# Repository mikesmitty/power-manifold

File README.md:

# Power Manifold

A six-port USB-C® power supply: USB Power Delivery 3.2, up to 100 W per port
from one 24 V supply, with per-port control, priority-based power sharing
and Home Assistant support. This repository holds the hardware (KiCad), the
firmware and the documentation site.

**Documentation:** <https://docs.powermanifold.io/>

- [First-time setup](https://docs.powermanifold.io/setup/first-time-setup/)
- [User guide](https://docs.powermanifold.io/guide/front-panel/)
- [Integrations](https://docs.powermanifold.io/integrations/mqtt/): MQTT,
  Home Assistant and the HTTP API
- [Hardware architecture](https://docs.powermanifold.io/developers/architecture/)

## Repository layout

| Path | Contents |
| --- | --- |
| `hardware/backplane` | Backplane KiCad project |
| `hardware/backplane-backer` | Insulating FR4 backer plate between the backplane and the rear wall |
| `hardware/charger-module` | Charger blade KiCad project |
| `hardware/controller` | Management controller card KiCad project |
| `hardware/left-side-plate` | Left chassis side plate, fabricated as a bare PCB |
| `hardware/pcie-breakout` | Pico 2 W development carrier for the management slot |
| `hardware/status-strip` | Front-panel status LED strip |
| `hardware/libraries` | Shared KiCad symbols and footprints |
| `hardware/CAD` | STEP exports of the boards |
| `firmware/controller` | Management controller firmware (RP2350) and its host tests |
| `firmware/charger-module` | Charger blade firmware (STM32G071) and its host tests |
| `firmware/update-proxy` | Cloudflare Worker that serves controller update images |
| `docs` | The documentation site (Astro and Starlight) |

Each firmware directory has a short README with build commands. Its full
developer documentation is in its `docs/` directory and is published on the
documentation site.

CI exports KiCad fabrication outputs when a board changes, and
release-please cuts a release for each component.

## License

Copyright 2024-2026 Michael Smith.

| Part | License |
| --- | --- |
| Hardware designs in `hardware/` | CERN-OHL-P-2.0 ([LICENSE-hardware](LICENSE-hardware)) |
| Documentation: Markdown files (`.md`, `.mdx`), the screenshots in `docs/src/assets/` and the site icon `docs/public/favicon.svg` | CC BY 4.0 ([LICENSE-docs](LICENSE-docs)) |
| Product renders: the images in `img/` and `docs/public/hero.webp` | None, all rights reserved |
| Everything else, including the firmware, the web page, the tools and the code of the documentation site | MIT ([LICENSE](LICENSE)) |

Third-party material keeps its own terms:

- `hardware/libraries/`: symbols, footprints and 3D models, most of them
  from the KiCad libraries, EasyEDA and part makers.
- Third-party 3D models and fonts embedded in the board files, and the
  3D models inside the board exports in `hardware/CAD/`.
- `hardware/licenses/`: the license texts for the openly licensed parts
  above, which [hardware/THIRD-PARTY.md](hardware/THIRD-PARTY.md) lists with
  their notices.
- `firmware/controller/lib/monocypher/`: CC0 or BSD-2-Clause, see its
  `LICENCE.md`.
- `firmware/tools/licenses/`: the license files of newlib and libgloss, the
  C library the firmware links, for the notices below.

Libraries that the firmware builds download, such as the Pico SDK and ST's
USB-PD stack, are not part of this repository. Each firmware release lists them in
its SBOM (`.cdx.json`) and carries their copyright notices and license texts in
a notices file (`controller-notices.txt`, `charger-module-notices.txt`).

Power Manifold is a trademark of Idle Curiosity LLC. The licenses above cover
the designs, code and documentation, not the name: a product built or modified
from this repository may say it is based on Power Manifold, but may not be sold
or distributed under that name.

USB Type-C® and USB-C® are registered trademarks of USB Implementers Forum.

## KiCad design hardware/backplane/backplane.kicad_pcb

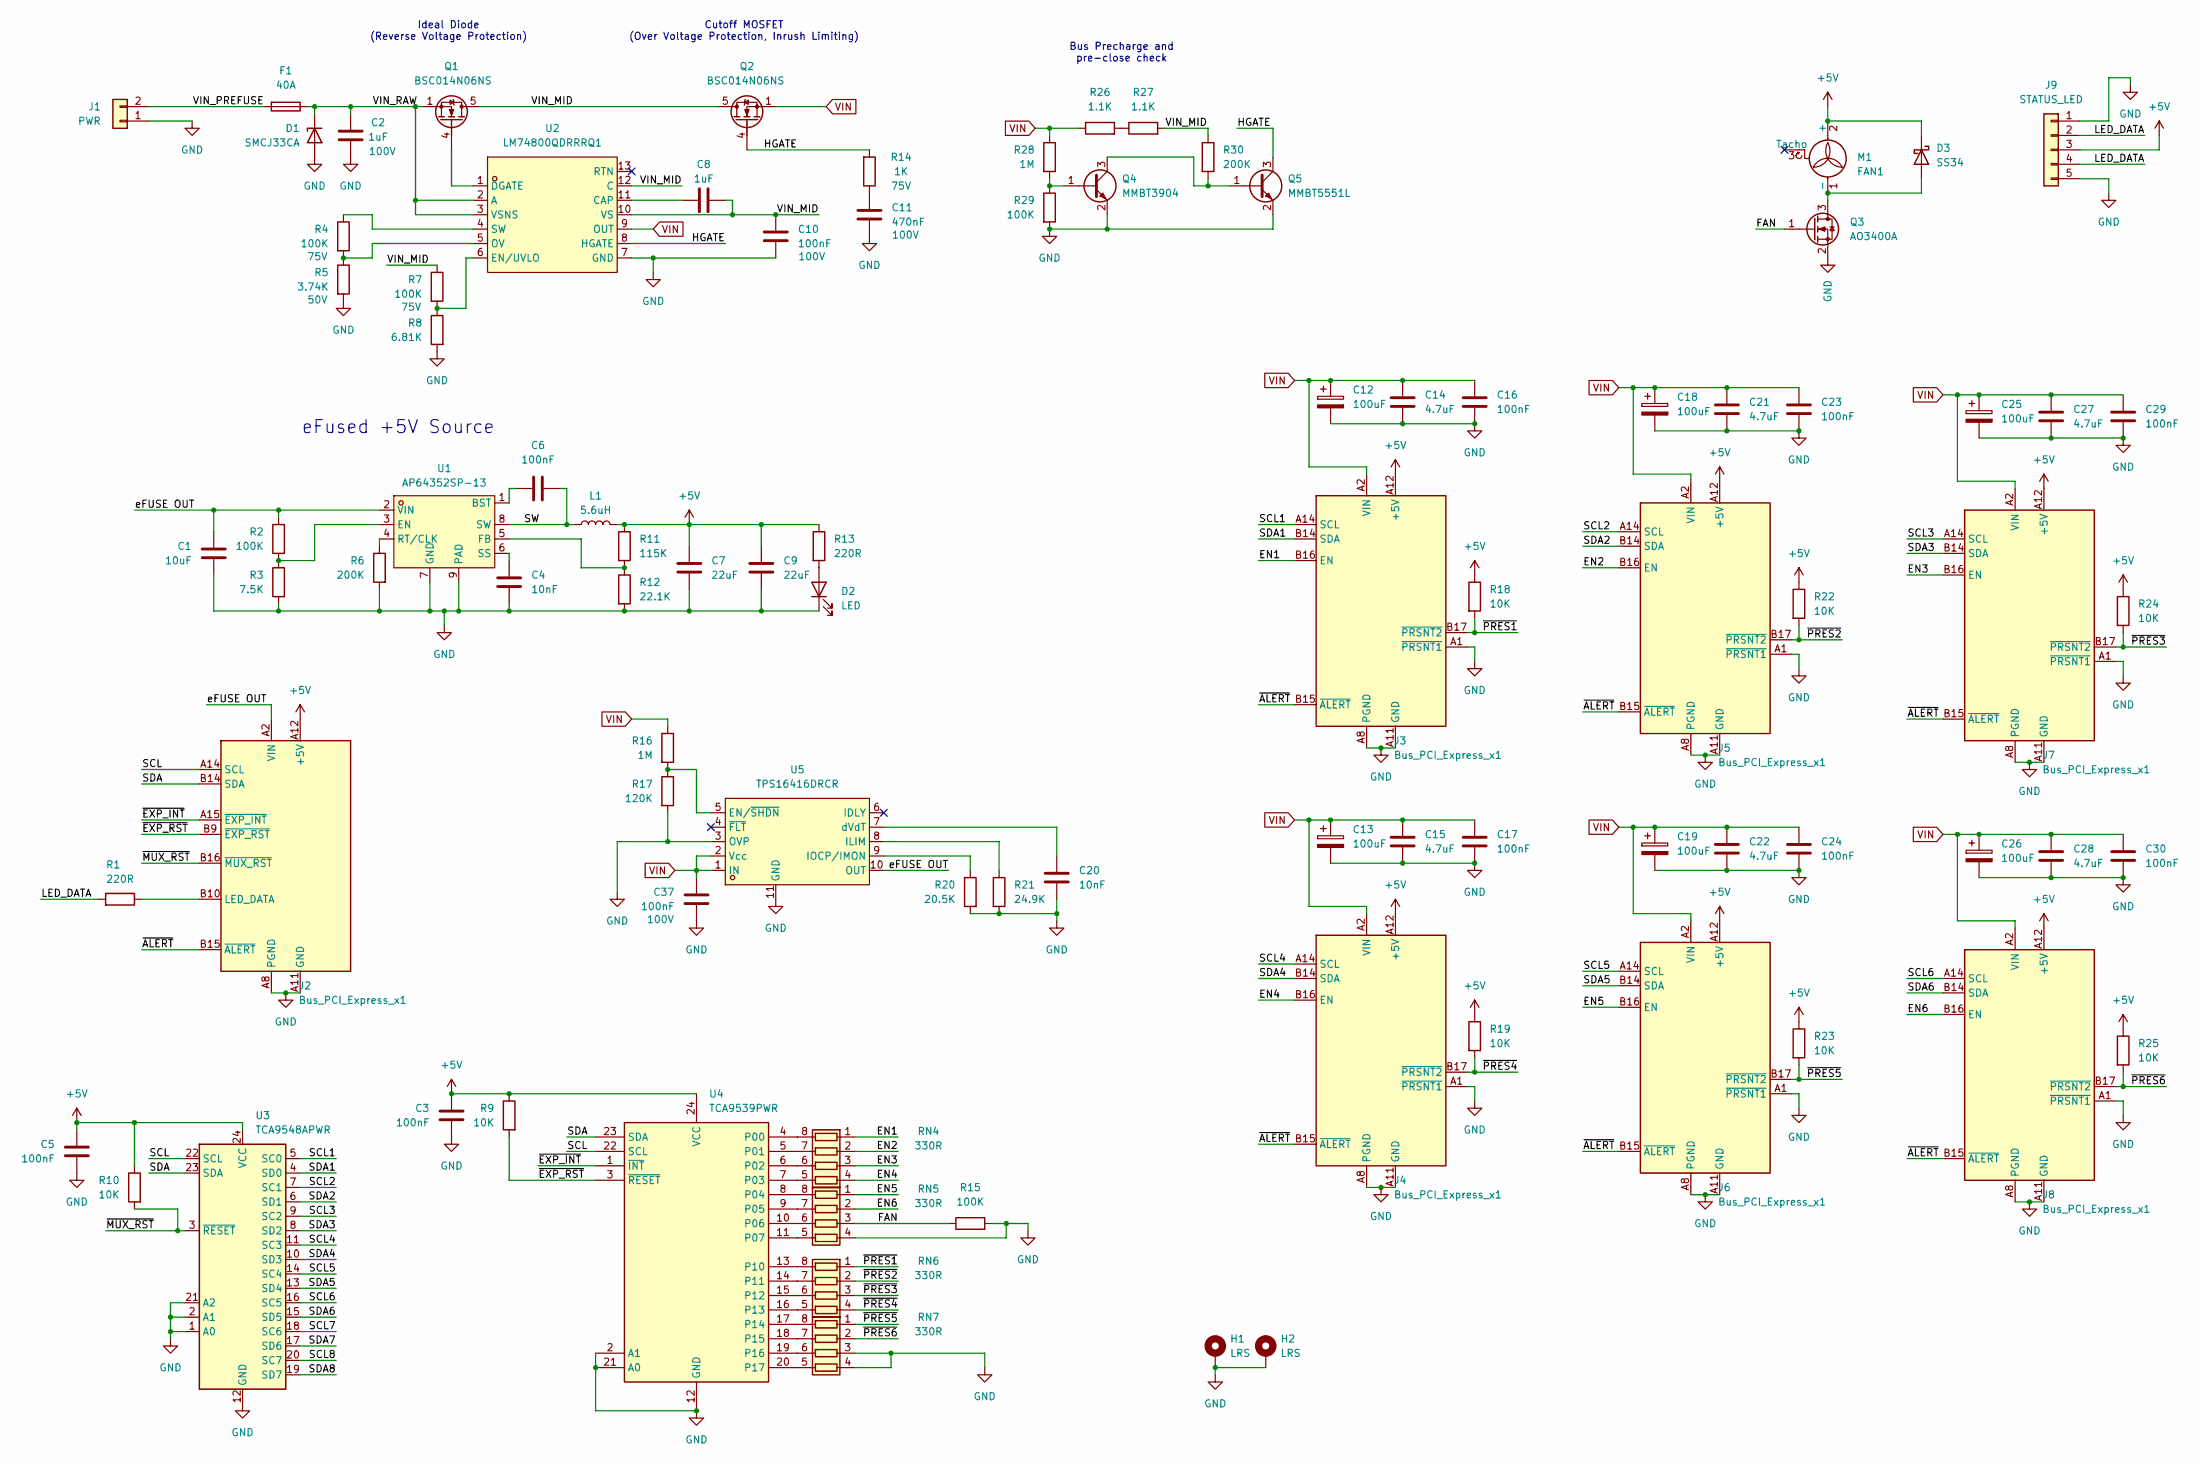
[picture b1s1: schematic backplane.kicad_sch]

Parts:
C1: 10uF; C_0805_2012Metric; LCSC C440198
C2: 1uF; C_0805_2012Metric; Voltage 100V; LCSC C5370002
C3, C5, C6, C16, C17, C23, C24, C29, C30: 100nF; C_0402_1005Metric; LCSC C307331
C4, C20: 10nF; C_0402_1005Metric; LCSC C15195
C7, C9: 22uF; C_0805_2012Metric; LCSC C45783
C8: 1uF; C_0402_1005Metric; LCSC C52923
C10, C37: 100nF; C_0603_1608Metric; Voltage 100V; LCSC C88219
C11: 470nF; C_0805_2012Metric; Voltage 100V; LCSC C596323
C12, C13, C18, C19, C25, C26: 100uF; CP_Elec_6.3x7.7; LCSC C3151829
C14, C15, C21, C22, C27, C28: 4.7uF; C_1206_3216Metric; LCSC C29823
D1: SMCJ33CA; D_SMC; LCSC C310048
D2: LED; LED_0603_1608Metric; LCSC C2286
D3: SS34; D_SMA; LCSC C8678
F1: 40A; FUSE-SMD_L6.1-W2.5; LCSC C2762486
H1, H2: LRS; MountingHole_4.3mm_M4_Pad_Via
J1: PWR; AMASS_XT60PW-M_1x02_P7.20mm_Horizontal; LCSC C98732
J2, J3, J4, J5, J6, J7, J8: Bus_PCI_Express_x1; AMPHENOL_PCI_E_10018783-10210TLF; LCSC C4693418
J9: STATUS_LED; JST_SH_BM05B-SRSS-TB_1x05-1MP_P1.00mm_Vertical; LCSC C160391
L1: 5.6uH; L_Sunlord_MWSA0603S; LCSC C408448
M1: FAN1; FanPinHeader_1x03_P2.54mm_Vertical; LCSC C234181
Q1, Q2: BSC014N06NS; Infineon_PG-TDSON-8_6.15x5.15mm; LCSC C113391
Q3: AO3400A; SOT-23; LCSC C20917
Q4: MMBT3904; SOT-23; LCSC C20526
Q5: MMBT5551L; SOT-23; LCSC C2145
R1, R13: 220R; R_0402_1005Metric; LCSC C25091
R2, R15: 100K; R_0402_1005Metric; LCSC C25741
R3: 7.5K; R_0402_1005Metric; LCSC C25918
R4, R7: 100K; R_0603_1608Metric; Voltage 75V; LCSC C25803
R5: 3.74K; R_0402_1005Metric; Voltage 50V; LCSC C15172
R6, R30: 200K; R_0402_1005Metric; LCSC C25764
R8: 6.81K; R_0603_1608Metric; LCSC C2930121
R9, R10, R18, R19, R22, R23, R24, R25: 10K; R_0402_1005Metric; LCSC C25744
R11: 115K; R_0402_1005Metric; LCSC C25747
R12: 22.1K; R_0402_1005Metric; LCSC C163478
R14: 1K; R_0603_1608Metric; Voltage 75V; LCSC C21190
R16, R28: 1M; R_0603_1608Metric; LCSC C22935
R17: 120K; R_0603_1608Metric; LCSC C25808
R20: 20.5K; R_0402_1005Metric; LCSC C57105
R21: 24.9K; R_0402_1005Metric; LCSC C25874
R26, R27: 1.1K; R_1206_3216Metric; LCSC C2933580
R29: 100K; R_0603_1608Metric; LCSC C25803
RN4, RN5, RN6, RN7: 330R; R_Array_Concave_4x0402; LCSC C43557
U1: AP64352SP-13; Diodes_SO-8EP; LCSC C2071665
U2: LM74800QDRRRQ1; WSON-12_L3.0-W3.0-P0.50-TL-EP-2; LCSC C3215600
U3: TCA9548APWR; TSSOP-24_4.4x7.8mm_P0.65mm; LCSC C130026
U4: TCA9539PWR; TSSOP-24_4.4x7.8mm_P0.65mm; LCSC C131972
U5: TPS16416DRCR; VSON-10_L3.0-W3.0-P0.50-TL-EP; MPN TPS16416DRCR; LCSC C22433503

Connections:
+5V: C3.1, C5.1, C7.1, C9.1, D3.1 (K), J2.A12 (+5V), J2.B12 (+5V), J3.A12 (+5V), J3.B12 (+5V), J4.A12 (+5V), J4.B12 (+5V), J5.A12 (+5V), J5.B12 (+5V), J6.A12 (+5V), J6.B12 (+5V), J7.A12 (+5V), J7.B12 (+5V), J8.A12 (+5V), J8.B12 (+5V), J9.3, L1.2, M1.2 (+), R9.1, R10.1, R11.1, R13.1, R18.1, R19.1, R22.1, R23.1, R24.1, R25.1, U3.24 (VCC), U4.24 (VCC)
/EN1: J3.B16 (EN), RN4.1 (R1.1)
/EN2: J5.B16 (EN), RN4.2 (R2.1)
/EN3: J7.B16 (EN), RN4.3 (R3.1)
/EN4: J4.B16 (EN), RN4.4 (R4.1)
/EN5: J6.B16 (EN), RN5.1 (R1.1)
/EN6: J8.B16 (EN), RN5.2 (R2.1)
/FAN: Q3.1 (G), R15.1, RN5.3 (R3.1)
/HGATE: Q2.4 (G), Q5.3 (C), R14.2, U2.8 (HGATE)
/LED_DATA: J9.2, J9.4, R1.2
/SCL: J2.A14 (SCL), U3.22 (SCL), U4.22 (SCL)
/SCL1: J3.A14 (SCL), U3.5 (SC0)
/SCL2: J5.A14 (SCL), U3.7 (SC1)
/SCL3: J7.A14 (SCL), U3.9 (SC2)
/SCL4: J4.A14 (SCL), U3.11 (SC3)
/SCL5: J6.A14 (SCL), U3.14 (SC4)
/SCL6: J8.A14 (SCL), U3.16 (SC5)
/SCL7: U3.18 (SC6)
/SCL8: U3.20 (SC7)
/SDA: J2.B14 (SDA), U3.23 (SDA), U4.23 (SDA)
/SDA1: J3.B14 (SDA), U3.4 (SD0)
/SDA2: J5.B14 (SDA), U3.6 (SD1)
/SDA3: J7.B14 (SDA), U3.8 (SD2)
/SDA4: J4.B14 (SDA), U3.10 (SD3)
/SDA5: J6.B14 (SDA), U3.13 (SD4)
/SDA6: J8.B14 (SDA), U3.15 (SD5)
/SDA7: U3.17 (SD6)
/SDA8: U3.19 (SD7)
/SW: C6.2, L1.1, U1.8 (SW)
/VIN_MID: C8.2, C10.1, Q1.5 (D), Q2.5 (D), R7.1, R27.2, R30.1, U2.10 (VS), U2.12 (C)
/VIN_PREFUSE: F1.2, J1.2
/VIN_RAW: C2.1, D1.1 (K), F1.1, Q1.1 (S), Q1.2 (S), Q1.3 (S), U2.2 (A), U2.3 (VSNS)
/eFUSE OUT: C1.1, J2.A2 (VIN), J2.A3 (VIN), J2.A4 (VIN), J2.A5 (VIN), J2.A6 (VIN), J2.A7 (VIN), R2.1, U1.2 (VIN), U5.10 (OUT)
/~ALERT: J2.B15 (~ALERT), J3.B15 (~ALERT), J4.B15 (~ALERT), J5.B15 (~ALERT), J6.B15 (~ALERT), J7.B15 (~ALERT), J8.B15 (~ALERT)
/~EXP_INT: J2.A15 (~EXP_INT), U4.1 (~INT)
/~EXP_RST: J2.B9 (~EXP_RST), R9.2, U4.3 (~RESET)
/~MUX_RST: J2.B16 (~MUX_RST), R10.2, U3.3 (~RESET)
/~PRES1: J3.B17 (~PRSNT2), R18.2, RN6.1 (R1.1)
/~PRES2: J5.B17 (~PRSNT2), R22.2, RN6.2 (R2.1)
/~PRES3: J7.B17 (~PRSNT2), R24.2, RN6.3 (R3.1)
/~PRES4: J4.B17 (~PRSNT2), R19.2, RN6.4 (R4.1)
/~PRES5: J6.B17 (~PRSNT2), R23.2, RN7.1 (R1.1)
/~PRES6: J8.B17 (~PRSNT2), R25.2, RN7.2 (R2.1)
GND: C1.2, C2.2, C3.2, C4.1, C5.2, C7.2, C9.2, C10.2, C11.2, C12.2, C13.2, C14.2, C15.2, C16.2, C17.2, C18.2, C19.2, C20.1, C21.2, C22.2, C23.2, C24.2, C25.2, C26.2, C27.2, C28.2, C29.2, C30.2, C37.2, D1.2 (A), D2.1 (K), H1.1 (1_1), H2.1 (1_1), J1.1, J2.A1 (GND), J2.A8 (PGND), J2.A9 (PGND), J2.A10 (PGND), J2.A11 (GND), J2.A13 (GND), J2.A16 (GND), J2.A17 (GND), J2.A18 (GND), J2.B1 (PGND), J2.B2 (PGND), J2.B3 (PGND), J2.B4 (PGND), J2.B5 (PGND), J2.B6 (PGND), J2.B7 (PGND), J2.B8 (PGND), J2.B11 (GND), J2.B13 (GND), J2.B17 (GND), J2.B18 (GND), J3.A1 (~PRSNT1), J3.A8 (PGND), J3.A9 (PGND), J3.A10 (PGND), J3.A11 (GND), J3.A13 (GND), J3.A15 (GND), J3.A16 (GND), J3.A17 (GND), J3.A18 (GND), J3.B1 (PGND), J3.B2 (PGND), J3.B3 (PGND), J3.B4 (PGND), J3.B5 (PGND), J3.B6 (PGND), J3.B7 (PGND), J3.B8 (PGND), J3.B9 (PGND), J3.B10 (GND), J3.B11 (GND), J3.B13 (GND), J3.B18 (GND), J4.A1 (~PRSNT1), J4.A8 (PGND), J4.A9 (PGND), J4.A10 (PGND), J4.A11 (GND), J4.A13 (GND), J4.A15 (GND), J4.A16 (GND), J4.A17 (GND), J4.A18 (GND), J4.B1 (PGND), J4.B2 (PGND), J4.B3 (PGND), J4.B4 (PGND), J4.B5 (PGND), J4.B6 (PGND), J4.B7 (PGND), J4.B8 (PGND), J4.B9 (PGND), J4.B10 (GND), J4.B11 (GND), J4.B13 (GND), J4.B18 (GND), J5.A1 (~PRSNT1), J5.A8 (PGND), J5.A9 (PGND), J5.A10 (PGND), J5.A11 (GND), J5.A13 (GND), J5.A15 (GND), J5.A16 (GND), J5.A17 (GND), J5.A18 (GND), J5.B1 (PGND), J5.B2 (PGND), J5.B3 (PGND), J5.B4 (PGND), J5.B5 (PGND), J5.B6 (PGND), J5.B7 (PGND), J5.B8 (PGND), J5.B9 (PGND), J5.B10 (GND), J5.B11 (GND), J5.B13 (GND), J5.B18 (GND), J6.A1 (~PRSNT1), J6.A8 (PGND), J6.A9 (PGND), J6.A10 (PGND), J6.A11 (GND), J6.A13 (GND), J6.A15 (GND), J6.A16 (GND), J6.A17 (GND), J6.A18 (GND), J6.B1 (PGND), J6.B2 (PGND), J6.B3 (PGND), J6.B4 (PGND), J6.B5 (PGND), J6.B6 (PGND), J6.B7 (PGND), J6.B8 (PGND), J6.B9 (PGND), J6.B10 (GND), J6.B11 (GND), J6.B13 (GND), J6.B18 (GND), J7.A1 (~PRSNT1), J7.A8 (PGND), J7.A9 (PGND), J7.A10 (PGND), J7.A11 (GND), J7.A13 (GND), J7.A15 (GND), J7.A16 (GND), J7.A17 (GND), J7.A18 (GND), J7.B1 (PGND), J7.B2 (PGND), J7.B3 (PGND), J7.B4 (PGND), J7.B5 (PGND), J7.B6 (PGND), J7.B7 (PGND), J7.B8 (PGND), J7.B9 (PGND), J7.B10 (GND), J7.B11 (GND), J7.B13 (GND), J7.B18 (GND), J8.A1 (~PRSNT1), J8.A8 (PGND), J8.A9 (PGND), J8.A10 (PGND), J8.A11 (GND), J8.A13 (GND), J8.A15 (GND), J8.A16 (GND), J8.A17 (GND), J8.A18 (GND), J8.B1 (PGND), J8.B2 (PGND), J8.B3 (PGND), J8.B4 (PGND), J8.B5 (PGND), J8.B6 (PGND), J8.B7 (PGND), J8.B8 (PGND), J8.B9 (PGND), J8.B10 (GND), J8.B11 (GND), J8.B13 (GND), J8.B18 (GND), J9.1, J9.5, Q3.2 (S), Q4.2 (E), Q5.2 (E), R3.2, R5.2, R6.2, R8.2, R12.2, R15.2, R17.2, R20.2, R21.2, R29.2, RN5.4 (R4.1), RN7.3 (R3.1), RN7.4 (R4.1), U1.7 (GND), U1.9 (PAD), U2.7 (GND), U3.1 (A0), U3.2 (A1), U3.12 (GND), U3.21 (A2), U4.2 (A1), U4.12 (GND), U4.21 (A0), U5.3 (OVP), U5.11 (GND)
unnamed: C11.1, R14.1
unnamed: D2.2 (A), R13.2
unnamed: D3.2 (A), M1.1 (-), Q3.3 (D)
unnamed: J2.B10 (LED_DATA), R1.1
unnamed: Q1.4 (G), U2.1 (DGATE)
unnamed: Q4.1 (B), R28.2, R29.1
unnamed: Q4.3 (C), Q5.1 (B), R30.2
unnamed: R26.2, R27.1
unnamed: RN4.8 (R1.2), U4.4 (P00)
unnamed: RN4.7 (R2.2), U4.5 (P01)
unnamed: RN4.6 (R3.2), U4.6 (P02)
unnamed: RN4.5 (R4.2), U4.7 (P03)
unnamed: RN5.8 (R1.2), U4.8 (P04)
unnamed: RN5.7 (R2.2), U4.9 (P05)
unnamed: RN5.6 (R3.2), U4.10 (P06)
unnamed: RN5.5 (R4.2), U4.11 (P07)
unnamed: RN6.8 (R1.2), U4.13 (P10)
unnamed: RN6.7 (R2.2), U4.14 (P11)
unnamed: RN6.6 (R3.2), U4.15 (P12)
unnamed: RN6.5 (R4.2), U4.16 (P13)
unnamed: RN7.8 (R1.2), U4.17 (P14)
unnamed: RN7.7 (R2.2), U4.18 (P15)
unnamed: RN7.6 (R3.2), U4.19 (P16)
unnamed: RN7.5 (R4.2), U4.20 (P17)
unnamed: C6.1, U1.1 (BST)
unnamed: R2.2, R3.1, U1.3 (EN)
unnamed: R11.2, R12.1, U1.5 (FB)
unnamed: R6.1, U1.4 (RT/CLK)
unnamed: C4.2, U1.6 (SS)
unnamed: C8.1, U2.11 (CAP)
unnamed: R7.2, R8.1, U2.6 (EN/UVLO)
unnamed: R4.2, R5.1, U2.5 (OV)
unnamed: R4.1, U2.4 (SW)
unnamed: R16.2, R17.1, U5.5 (EN/~SHDN)
unnamed: R21.1, U5.8 (ILIM)
unnamed: R20.1, U5.9 (IOCP/IMON)
unnamed: C20.2, U5.7 (dVdT)
VIN: C12.1, C13.1, C14.1, C15.1, C16.1, C17.1, C18.1, C19.1, C21.1, C22.1, C23.1, C24.1, C25.1, C26.1, C27.1, C28.1, C29.1, C30.1, C37.1, J3.A2 (VIN), J3.A3 (VIN), J3.A4 (VIN), J3.A5 (VIN), J3.A6 (VIN), J3.A7 (VIN), J4.A2 (VIN), J4.A3 (VIN), J4.A4 (VIN), J4.A5 (VIN), J4.A6 (VIN), J4.A7 (VIN), J5.A2 (VIN), J5.A3 (VIN), J5.A4 (VIN), J5.A5 (VIN), J5.A6 (VIN), J5.A7 (VIN), J6.A2 (VIN), J6.A3 (VIN), J6.A4 (VIN), J6.A5 (VIN), J6.A6 (VIN), J6.A7 (VIN), J7.A2 (VIN), J7.A3 (VIN), J7.A4 (VIN), J7.A5 (VIN), J7.A6 (VIN), J7.A7 (VIN), J8.A2 (VIN), J8.A3 (VIN), J8.A4 (VIN), J8.A5 (VIN), J8.A6 (VIN), J8.A7 (VIN), Q2.1 (S), Q2.2 (S), Q2.3 (S), R16.1, R26.1, R28.1, U2.9 (OUT), U5.1 (IN), U5.2 (Vcc)

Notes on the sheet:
Bus Precharge and pre-close check
eFused +5V Source
Ideal Diode (Reverse Voltage Protection)
Cutoff MOSFET (Over Voltage Protection, Inrush Limiting)

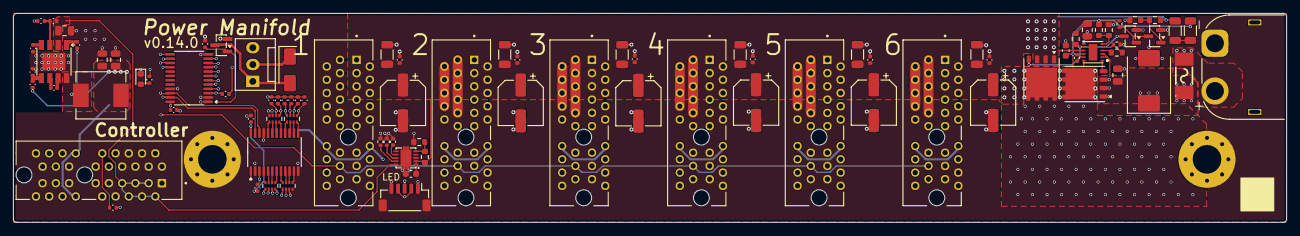
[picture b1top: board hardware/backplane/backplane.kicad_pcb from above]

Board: 4 copper layers, 192.0 x 31.5 mm, 92 parts (0 on the bottom side), 78 nets.

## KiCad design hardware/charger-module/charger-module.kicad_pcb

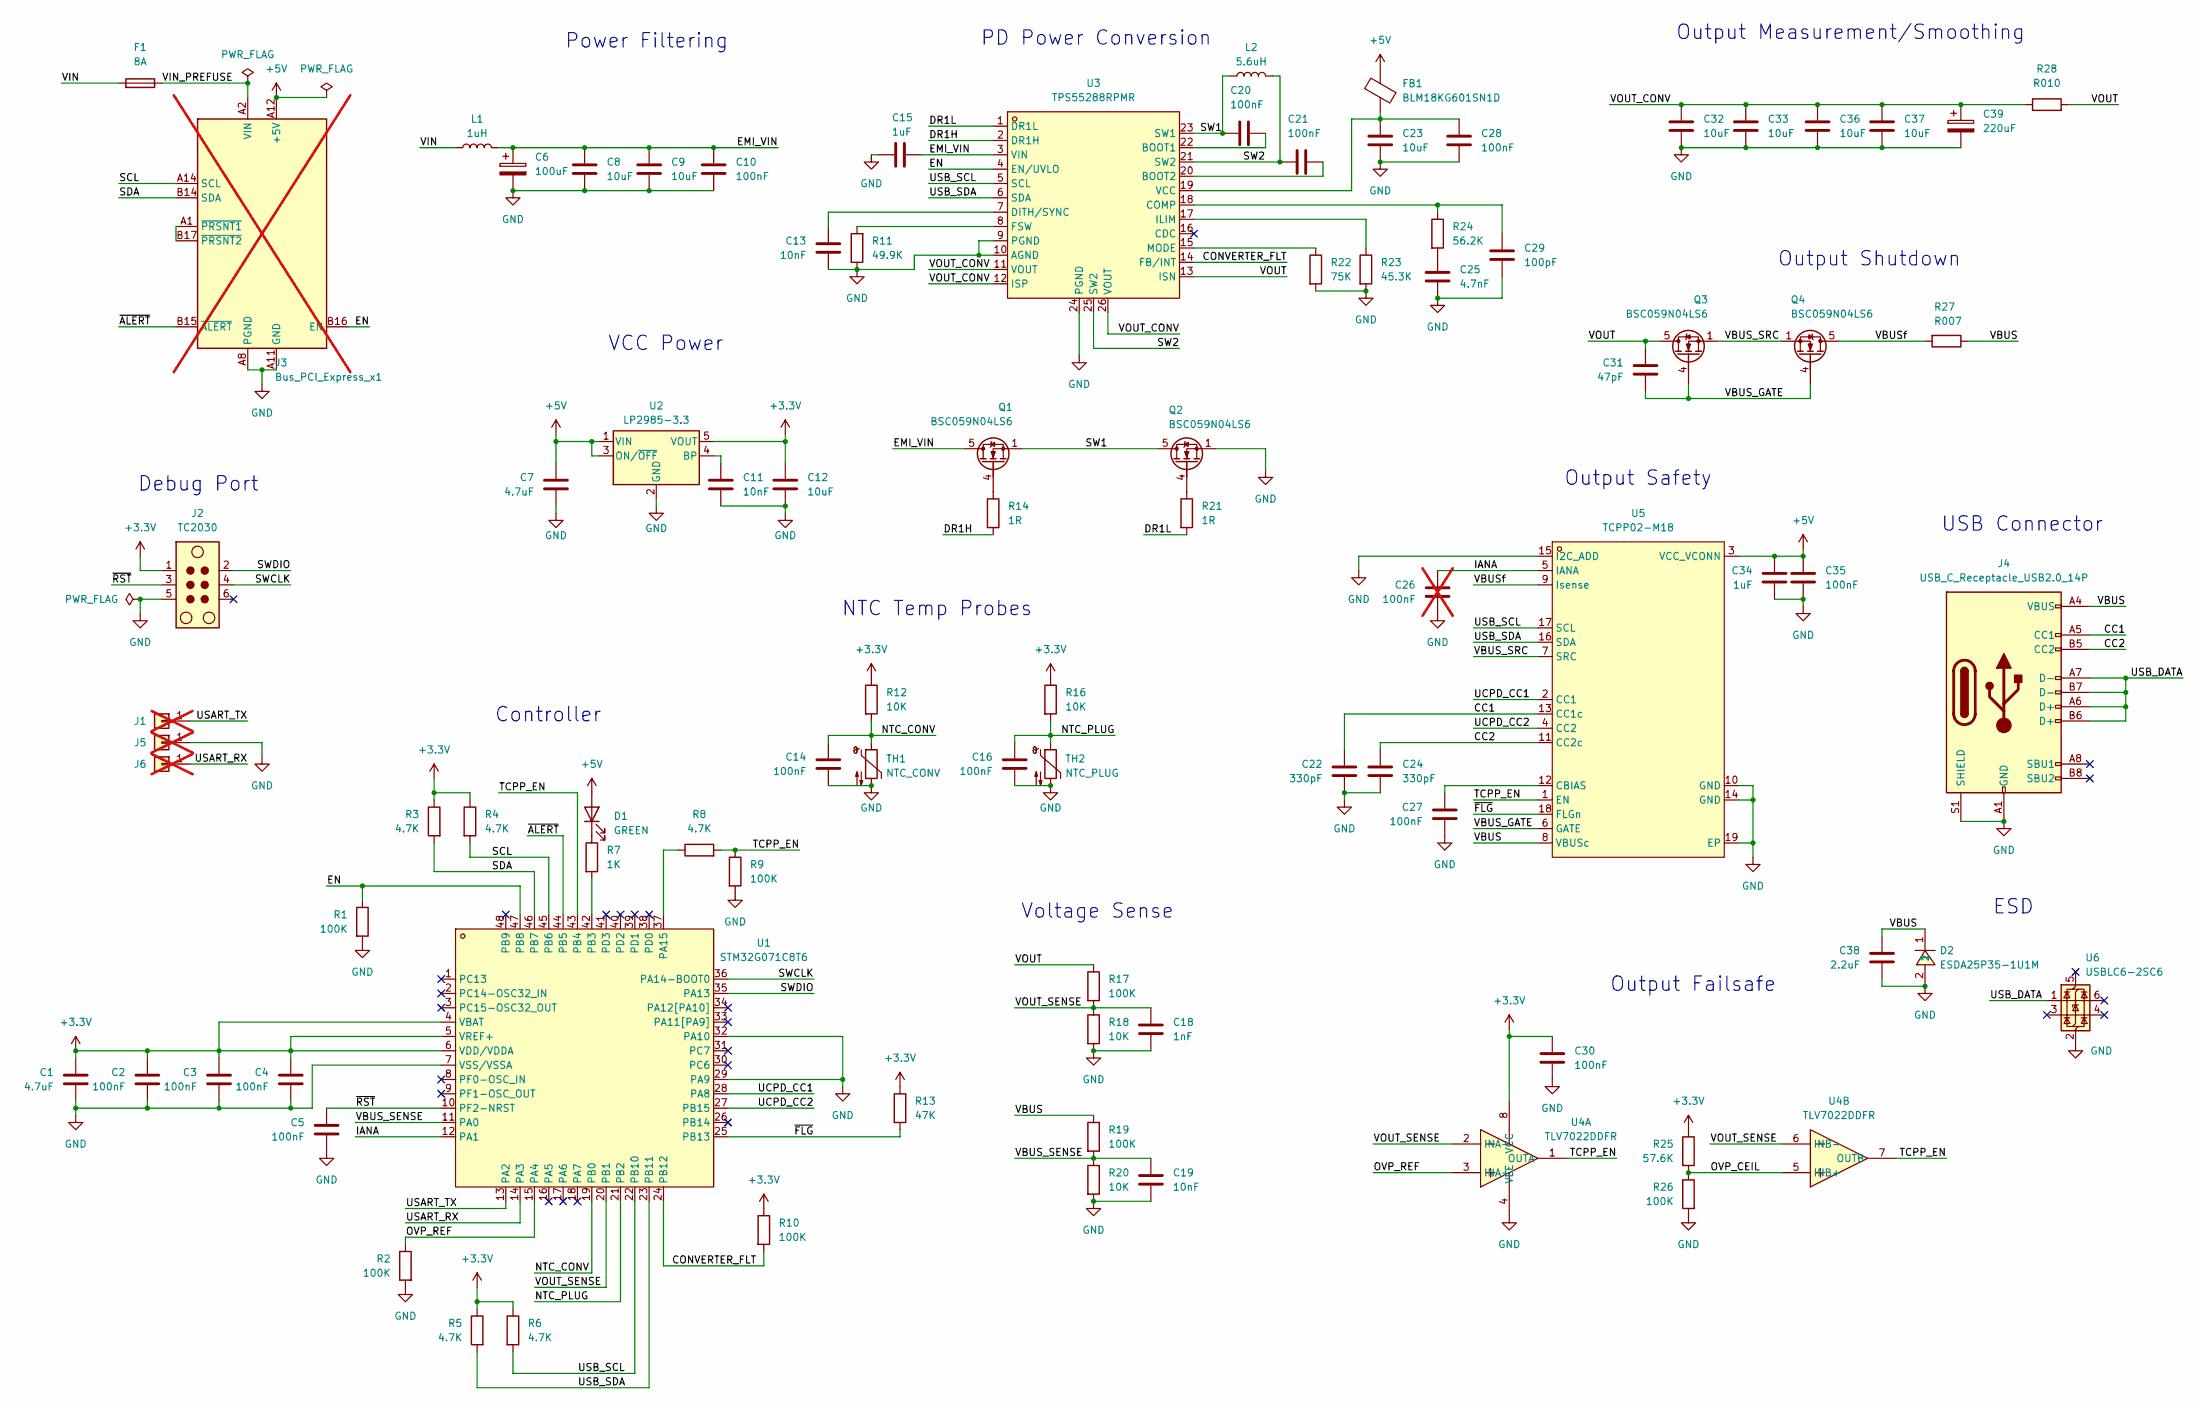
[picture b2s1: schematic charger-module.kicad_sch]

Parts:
C1, C7: 4.7uF; C_0603_1608Metric; LCSC C108342
C2, C3, C4, C5, C10, C14, C16, C27, C28, C30, C35: 100nF; C_0402_1005Metric; LCSC C307331
C6: 100uF; CP_Elec_6.3x7.7; LCSC C3151829
C8, C9, C32, C33, C36, C37: 10uF; C_1206_3216Metric; LCSC C89632
C11, C13, C19: 10nF; C_0402_1005Metric; LCSC C15195
C12: 10uF; C_0805_2012Metric; LCSC C95841
C15, C34: 1uF; C_0603_1608Metric; LCSC C5199872
C18: 1nF; C_0402_1005Metric; LCSC C1523
C20, C21: 100nF; C_0402_1005Metric; Voltage 50V; LCSC C307331
C22, C24: 330pF; C_0402_1005Metric; LCSC C13533
C23: 10uF; C_0805_2012Metric; LCSC C1713
C25: 4.7nF; C_0402_1005Metric; LCSC C1538
C26: 100nF; C_0402_1005Metric; LCSC C1525; not fitted
C29: 100pF; C_0402_1005Metric; LCSC C1546
C31: 47pF; C_0402_1005Metric; LCSC C1567
C38: 2.2uF; C_1206_3216Metric; LCSC C50254
C39: 220uF; CP_Elec_8x10; LCSC C46550469
D1: GREEN; LED_0603_1608Metric; LCSC C965804
D2: ESDA25P35-1U1M; DFN1610-2_L1.6-W1.0-P1.05-RD; MPN ESDA25P35-1U1M; LCSC Part C1974707
F1: 8A; FUSE-SMD_L6.1-W2.7; LCSC C142876
FB1: BLM18KG601SN1D; L_0603_1608Metric; LCSC C85833
J1: TX; TestPoint_Pad_D1.5mm; not fitted
J2: TC2030; Tag-Connect_TC2030-IDC-NL_2x03_P1.27mm_Vertical
J3: Bus_PCI_Express_x1; BUS_PCIexpress_x1; not fitted
J4: USB_C_Receptacle_USB2.0_14P; USB-C-SMD_GT-USB-7004; LCSC C2686968
J5: GND; TestPoint_Pad_D1.5mm; not fitted
J6: RX; TestPoint_Pad_D1.5mm; not fitted
L1: 1uH; L_Sunlord_MWSA0603S; LCSC C112125
L2: 5.6uH; L_Sunlord_MWSA1005S; LCSC C17700183
Q1, Q2, Q3, Q4: BSC059N04LS6; TDSON-8-1; LCSC C534356
R1, R2, R9, R10, R26: 100K; R_0402_1005Metric; LCSC C25741
R3, R4, R5, R6, R8: 4.7K; R_0402_1005Metric; LCSC C25900
R7: 1K; R_0402_1005Metric; LCSC C11702
R11: 49.9K; R_0402_1005Metric; LCSC C25897
R12, R16, R18, R20: 10K; R_0402_1005Metric; LCSC C25744
R13: 47K; R_0402_1005Metric; LCSC C25792
R14, R21: 1R; R_0402_1005Metric; LCSC C25086
R17, R19: 100K; R_0402_1005Metric; Voltage 50V; LCSC C25741
R22: 75K; R_0402_1005Metric; LCSC C25798
R23: 45.3K; R_0402_1005Metric; LCSC C2933099
R24: 56.2K; R_0402_1005Metric; LCSC C54968
R25: 57.6K; R_0402_1005Metric; LCSC C2960799
R27: R007; R_1206_3216Metric; LCSC C7420011
R28: R010; R_1206_3216Metric; LCSC C105362
TH1: NTC_CONV; R_0603_1608Metric; LCSC C52155402
TH2: NTC_PLUG; R_0603_1608Metric; LCSC C52155402
U1: STM32G071C8T6; LQFP-48_L7.0-W7.0-P0.50-LS9.0-BL; MPN STM32G071C8T6; LCSC C529341
U2: LP2985-3.3; SOT-23-5; LCSC C89826
U3: TPS55288RPMR; VQFN-HR-26_L4.0-W3.5_TPS55288RPMR; MPN TPS55288RPMR; LCSC Part C2864583
U4: TLV7022DDFR; SOT-23-8_L2.9-W1.6-P0.65-LS2.8-BR; MPN TLV7022DDFR; LCSC Part C2862588
U5: TCPP02-M18; QFN-18_L3.5-W3.5-P0.50-TL-EP2.2; MPN TCPP02-M18; LCSC Part C3662929
U6: USBLC6-2SC6; SOT-23-6; LCSC C2687116

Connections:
+3.3V: C1.1, C2.1, C3.1, C4.1, C12.1, C30.1, J2.1, R3.1, R4.1, R5.1, R6.1, R10.1, R12.1, R13.1, R16.1, R25.1, U1.4 (VBAT), U1.5 (VREF+), U1.6 (VDD/VDDA), U2.5 (VOUT), U4.8 (VCC)
+5V: C7.1, C34.1, C35.1, D1.2 (A), FB1.2, J3.A12 (+5V), J3.B12 (+5V), U2.1 (VIN), U2.3 (ON/~OFF), U5.3 (VCC_VCONN)
/CC1: C22.1, J4.A5 (CC1), U5.13 (CC1c)
/CC2: C24.1, J4.B5 (CC2), U5.11 (CC2c)
/CONVERTER_FLT: R10.2, U1.24 (PB12), U3.14 (FB/INT)
/DR1H: R14.2, U3.2 (DR1H)
/DR1L: R21.2, U3.1 (DR1L)
/EMI_VIN: C6.1, C8.1, C9.1, C10.1, C15.1, L1.2, Q1.5 (D), U3.3 (VIN)
/EN: J3.B16 (EN), R1.1, U1.47 (PB8), U3.4 (EN/UVLO)
/IANA: C26.1, U1.12 (PA1), U5.5 (IANA)
/NTC_CONV: C14.1, R12.2, TH1.1, U1.19 (PB0)
/NTC_PLUG: C16.1, R16.2, TH2.1, U1.21 (PB2)
/OVP_CEIL: R25.2, R26.1, U4.5 (INB+)
/OVP_REF: R2.1, U1.15 (PA4), U4.3 (INA+)
/SCL: J3.A14 (SCL), R4.2, U1.45 (PB6)
/SDA: J3.B14 (SDA), R3.2, U1.46 (PB7)
/SW1: C20.1, L2.1, Q1.1 (S), Q1.2 (S), Q1.3 (S), Q2.5 (D), U3.23 (SW1)
/SW2: C21.1, L2.2, U3.21 (SW2), U3.25 (SW2)
/SWCLK: J2.4, U1.36 (PA14-BOOT0)
/SWDIO: J2.2, U1.35 (PA13)
/TCPP_EN: R8.2, R9.1, U1.43 (PB4), U4.1 (OUTA), U4.7 (OUTB), U5.1 (EN)
/UCPD_CC1: U1.28 (PA8), U5.2 (CC1)
/UCPD_CC2: U1.27 (PB15), U5.4 (CC2)
/USART_RX: J6.1 (Pin_1_1), U1.14 (PA3)
/USART_TX: J1.1 (Pin_1_1), U1.13 (PA2)
/USB_DATA: J4.A6 (D+), J4.A7 (D-), J4.B6 (D+), J4.B7 (D-), U6.1 (I/O1)
/USB_SCL: R6.2, U1.22 (PB10), U3.5 (SCL), U5.17 (SCL)
/USB_SDA: R5.2, U1.23 (PB11), U3.6 (SDA), U5.16 (SDA)
/VBUS: C38.1, D2.1, J4.A4 (VBUS), J4.A9 (VBUS), J4.B4 (VBUS), J4.B9 (VBUS), R19.1, R27.1, U5.8 (VBUSc)
/VBUS_GATE: C31.2, Q3.4 (G), Q4.4 (G), U5.6 (GATE)
/VBUS_SENSE: C19.1, R19.2, R20.1, U1.11 (PA0)
/VBUS_SRC: Q3.1 (S), Q3.2 (S), Q3.3 (S), Q4.1 (S), Q4.2 (S), Q4.3 (S), U5.7 (SRC)
/VBUSf: Q4.5 (D), R27.2, U5.9 (Isense)
/VIN: F1.2, L1.1
/VIN_PREFUSE: F1.1, J3.A2 (VIN), J3.A3 (VIN), J3.A4 (VIN), J3.A5 (VIN), J3.A6 (VIN), J3.A7 (VIN)
/VOUT: C31.1, Q3.5 (D), R17.1, R28.2, U3.13 (ISN)
/VOUT_CONV: C32.1, C33.1, C36.1, C37.1, C39.1, R28.1, U3.11 (VOUT), U3.12 (ISP), U3.26 (VOUT)
/VOUT_SENSE: C18.1, R17.2, R18.1, U1.20 (PB1), U4.2 (INA-), U4.6 (INB-)
/~ALERT: J3.B15 (~ALERT), U1.44 (PB5)
/~FLG: R13.2, U1.25 (PB13), U5.18 (FLGn)
/~RST: C5.1, J2.3, U1.10 (PF2-NRST)
GND: C1.2, C2.2, C3.2, C4.2, C5.2, C6.2, C7.2, C8.2, C9.2, C10.2, C11.2, C12.2, C13.2, C14.2, C15.2, C16.2, C18.2, C19.2, C22.2, C23.2, C24.2, C25.2, C26.2, C27.2, C28.2, C29.2, C30.2, C32.2, C33.2, C34.2, C35.2, C36.2, C37.2, C38.2, C39.2, D2.2, J2.5, J3.A8 (PGND), J3.A9 (PGND), J3.A10 (PGND), J3.A11 (GND), J3.A13 (GND), J3.A15 (GND), J3.A16 (GND), J3.A17 (GND), J3.A18 (GND), J3.B1 (PGND), J3.B2 (PGND), J3.B3 (PGND), J3.B4 (PGND), J3.B5 (PGND), J3.B6 (PGND), J3.B7 (PGND), J3.B8 (PGND), J3.B9 (PGND), J3.B10 (GND), J3.B11 (GND), J3.B13 (GND), J3.B18 (GND), J4.A1 (GND), J4.A12 (GND), J4.B1 (GND), J4.B12 (GND), J4.S1 (SHIELD), J5.1 (Pin_1_1), Q2.1 (S), Q2.2 (S), Q2.3 (S), R1.2, R2.2, R9.2, R11.1, R18.2, R20.2, R22.2, R23.2, R26.2, TH1.2, TH2.2, U1.7 (VSS/VSSA), U1.29 (PA9), U1.32 (PA10), U2.2 (GND), U3.9 (PGND), U3.10 (AGND), U3.24 (PGND), U4.4 (VEE), U5.10 (GND), U5.14 (GND), U5.15 (I2C_ADD), U5.19 (EP), U6.2 (GND)
unnamed: C25.1, R24.2
unnamed: D1.1 (K), R7.1
unnamed: J3.A1 (~PRSNT1), J3.B17 (~PRSNT2)
unnamed: Q1.4 (G), R14.1
unnamed: Q2.4 (G), R21.1
unnamed: R8.1, U1.37 (PA15)
unnamed: R7.2, U1.42 (PB3)
unnamed: C11.1, U2.4 (BP)
unnamed: C20.2, U3.22 (BOOT1)
unnamed: C21.2, U3.20 (BOOT2)
unnamed: C29.1, R24.1, U3.18 (COMP)
unnamed: C13.1, U3.7 (DITH/SYNC)
unnamed: R11.2, U3.8 (FSW)
unnamed: R23.1, U3.17 (ILIM)
unnamed: R22.1, U3.15 (MODE)
unnamed: C23.1, C28.1, FB1.1, U3.19 (VCC)
unnamed: C27.1, U5.12 (CBIAS)

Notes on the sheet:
ESD
Output Failsafe
VCC Power
Debug Port
Output Measurement/Smoothing
Output Shutdown
Controller
NTC Temp Probes
Power Filtering
Output Safety
PD Power Conversion
USB Connector
Voltage Sense

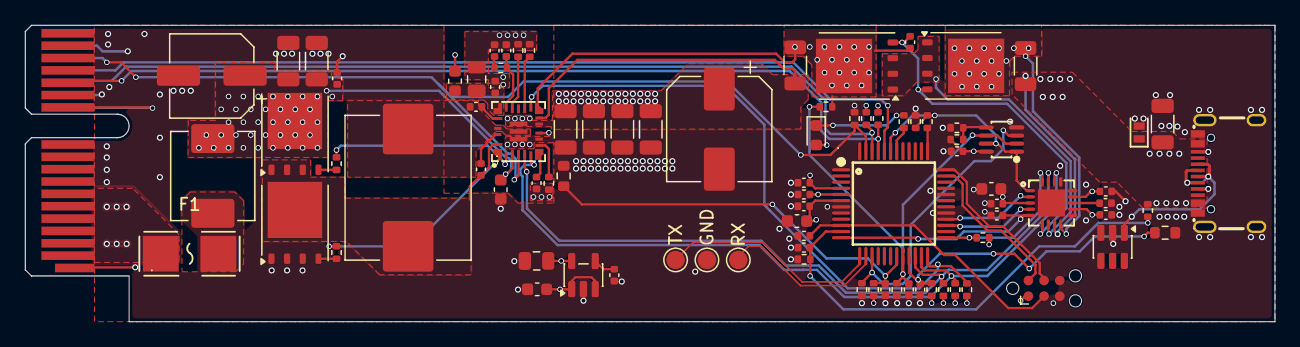
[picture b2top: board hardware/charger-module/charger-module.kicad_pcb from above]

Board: 4 copper layers, 101.2 x 24.0 mm, 89 parts (1 on the bottom side), 59 nets.

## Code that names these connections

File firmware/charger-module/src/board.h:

#pragma once

// Gen-3 charger blade, hardware/charger-module. Everything here is from the
// KiCad netlist of release 0.16.1 (exported 2026-09-29); pin functions from
// DS12232 Rev 5.
//
// U1 STM32G071C8T6 (LQFP48), no crystal: HSI16 runs the core and the UCPD.
//
//   PA0  VBUS_SENSE     ADC_IN0   receptacle VBUS, R19 100k / R20 10k, C19 10 nF
//   PA1  IANA           ADC_IN1   TCPP02 current monitor, 42 V/V across R27 7 mOhm
//   PA2  USART_TX       USART2    test pad J1 (also the ROM bootloader's USART2)
//   PA3  USART_RX       USART2    test pad J6
//   PA4  OVP_REF        DAC_OUT1  tracking OVP threshold into U4 INA+, R2 100k to GND
//   PA8  UCPD_CC1       UCPD1     through the TCPP02 CC switch
//   PA9  GND                      UCPD1_DBCC1, grounded: source-only port
//   PA10 GND                      UCPD1_DBCC2, grounded
//   PA13 SWDIO                    J2 Tag-Connect pin 2
//   PA14 SWCLK                    J2 pin 4
//   PA15 TCPP_EN drive            through R8 4.7k; R9 100k holds the line low
//   PB0  NTC_CONV       ADC_IN8   TH1 10k B3380 to GND, R12 10k to 3.3 V
//   PB1  VOUT_SENSE     ADC_IN9   converter output, R17 100k / R18 10k, C18 1 nF
//   PB2  NTC_PLUG       ADC_IN10  TH2, R16 10k to 3.3 V
//   PB3  LED            D1 green, anode on +5 V through R7 1k: low = lit
//   PB4  TCPP_EN sense            the line itself: low while an OVP comparator holds it
//   PB5  ALERT#                   J3 B15, open drain, pulled up by the controller
//   PB6  SCL            I2C1      J3 A14, backplane segment, R4 4.7k to 3.3 V
//   PB7  SDA            I2C1      J3 B14, R3 4.7k to 3.3 V
//   PB8  EN                       J3 B16, also TPS55288 EN/UVLO; R1 100k to GND
//   PB10 USB_SCL        I2C2      private bus: TPS55288 0x74, TCPP02 0x34; R6 4.7k
//   PB11 USB_SDA        I2C2      R5 4.7k
//   PB12 CONVERTER_FLT            TPS55288 FB/INT, low = fault, R10 100k to 3.3 V
//   PB13 FLG#                     TCPP02 FLGn, low = fault, R13 47k to 3.3 V
//   PB15 UCPD_CC2       UCPD1
//
// Every other pin is unconnected and stays in its reset state (analog).

// GPIOA
#define PIN_VBUS_SENSE      0
#define PIN_IANA            1
#define PIN_USART_TX        2
#define PIN_USART_RX        3
#define PIN_OVP_REF         4
#define PIN_TCPP_EN_DRV     15
// GPIOB
#define PIN_NTC_CONV        0
#define PIN_VOUT_SENSE      1
#define PIN_NTC_PLUG        2
#define PIN_LED             3
#define PIN_TCPP_EN_SENSE   4
#define PIN_ALERT_N         5
#define PIN_SCL             6
#define PIN_SDA             7
#define PIN_EN              8
#define PIN_USB_SCL         10
#define PIN_USB_SDA         11
#define PIN_CONVERTER_FLT   12
#define PIN_FLG_N           13

#define AF_USART2           1 // PA2, PA3
#define AF_I2C              6 // PB6/PB7 I2C1, PB10/PB11 I2C2

#define ADC_CH_VBUS         0
#define ADC_CH_IANA         1
#define ADC_CH_NTC_CONV     8
#define ADC_CH_VOUT         9
#define ADC_CH_NTC_PLUG     10
#define ADC_CH_TEMP         12 // internal temperature sensor
#define ADC_CH_VREFINT      13

// Private bus. The TPS55288's MODE pin carries R22 75k: external VCC, 0x74,
// PFM. The TCPP02's I2C_ADD pin is grounded.
#define ADDR_TPS55288       0x74
#define ADDR_TCPP02         0x34

// Analog scaling
#define SENSE_DIV_NUM       11      // (100k + 10k) / 10k, VBUS_SENSE and VOUT_SENSE
#define IANA_UV_PER_MA      294     // 42 V/V x 7 mOhm (R27)
// The IANA chain's gain as measured, per mille of the nominal one. The six
// blades on the bench read 2.2 to 4.8 % high at 5 A against an FNB58
// (2026-10-20); this is the middle of that spread, which puts every one of
// them within about 1.3 %.
#define IANA_GAIN_PER_MILLE 1035
#define CONV_SHUNT_UOHM     10000   // R28, TPS55288 ISP/ISN
#define NTC_PULLUP_OHM      10000   // R12, R16

// VBUS over-voltage comparator U4 (TLV7022), both halves open drain on
// TCPP_EN. Half A trips at OVP_REF x 11, set by the DAC; half B is the fixed
// ceiling from R25 57.6k / R26 100k off the 3.3 V rail: 2.094 V x 11 = 23.0 V,
// under the TCPP02's 24 V absolute maximum.
#define OVP_CEILING_MV      23000

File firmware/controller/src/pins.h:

#pragma once

// Controller GPIO map. Two boards run this firmware:
//   - the production controller card, hardware/controller: the default
//     PICO_BOARD=pwrman_controller_card (boards/), which defines
//     PWRMAN_CONTROLLER_CARD;
//   - the Pico 2 W on the pcie-breakout, a development stand-in until the
//     card exists (also the W6100-EVB-Pico2 in the same socket):
//     PICO_BOARD=pico2_w.
// I2C and the Ethernet pins are common to both; the other backplane signals
// and the reset drivers differ.
//
// GP16-GP21 are RESERVED for the wired-Ethernet path. WIZnet's EVB-Pico2
// boards put the Ethernet chip on SPI0 GP16-19 with RSTn=GP20 / INTn=GP21, so
// a W6100-EVB-Pico2 drops into the dev socket unchanged, and the controller
// card copies the same mapping so firmware carries over.

// The board header, which defines PWRMAN_CONTROLLER_CARD, comes in through
// pico.h. Without this, a file that included pins.h before any SDK header got
// the Pico 2 W map on the card (the input voltage monitor did, 2026-10-19).
#if __has_include("pico.h")
#include "pico.h"
#endif

#ifdef PWRMAN_CONTROLLER_CARD
// hardware/controller, from the KiCad netlist (2026-09-09)
#define PIN_EXP_RST_N   1  // TCA9539 reset, via Q1 (2N7002, 100k gate pull-down)
#define PIN_LED_DATA    2  // WS2812C light bar (7 pixels) through the backplane, via PIO
#define PIN_I2C_SDA     4  // I2C0 to backplane; 4.7k to 3.3 V on the card (R32)
#define PIN_I2C_SCL     5  // 4.7k to 3.3 V on the card (R41)
#define PIN_EXP_INT_N   6  // TCA9539 INT#: blade presence change (internal pull-up)
#define PIN_ALERT_N     7  // GLOBAL_ALERT#; 4.7k to 3.3 V on the card (R43)
#define PIN_MUX_RST_N   8  // TCA9548A reset, via Q2 (2N7002, 100k gate pull-down)
#define PIN_BUTTON      22 // front-panel button SW3 to GND (1k series, 100 nF), see button.h
#define PIN_VIN_SENSE   28 // ADC2: VIN through 120k / 10k (R13/R14), see vin.h
#define VIN_ADC_INPUT   2
// The reset lines are driven through N-channel FETs against the backplane's
// 10k pull-ups to 5 V: the GPIO drives a gate, so HIGH asserts the reset,
// and the RP2350's boot-time pad pull-down leaves both FETs off. A
// controller reboot therefore never resets the expander; the warm-start
// path (engine.c) relies on that.
#define RST_ASSERTED_LEVEL 1
#else
// Pico 2 W on the pcie-breakout: the breakout header's pins, push-pull
#define PIN_LED_DATA    2  // WS2812C light bar (7 pixels) through the backplane, via PIO
#define PIN_ALERT_N     3  // GLOBAL_ALERT#: wire-OR of all blade ALERT# lines
#define PIN_I2C_SDA     4  // I2C0 to backplane (TCA9548A + TCA9539 upstream side)
#define PIN_I2C_SCL     5
#define PIN_EXP_INT_N   6  // TCA9539 INT#: blade presence change
#define PIN_MUX_RST_N   7  // TCA9548A hardware reset
#define PIN_EXP_RST_N   8  // TCA9539 hardware reset
#define PIN_BUTTON      22 // no button on the carrier; a wire from GP22 to GND acts as one (button.h)
// The carrier drives the reset lines directly: LOW asserts. While the Pico
// itself is in reset, its pad pull-down against the backplane's 10k pull-up
// should still leave the line above the expander's input-high threshold
// (per datasheet; verify at bring-up), so a controller reboot does not
// reset the expander here either.
#define RST_ASSERTED_LEVEL 0
#endif

#define I2C_BUS         i2c0
#ifdef PWRMAN_INTERNAL_PULLUPS
// CARRIER_INTERNAL_PULLUPS: the RP2350 pad pull-ups (50-80k) stand in for the
// three 4.7k resistors on the breakout. Tens of kilohms into the bus
// capacitance is far too slow for 400 kHz; 100 kHz leaves the slow edges
// inside the low period, and once a mux channel is open that segment's 4.7k
// pull-ups stiffen the upstream side as well. Bench only, one or two blades
// (ran the 2026-09-23 bring-up).
#define I2C_BAUD        (100 * 1000)
#else
#define I2C_BAUD        (400 * 1000)
#endif

// Wired Ethernet: WIZnet W6100 on SPI0, the EVB-Pico2 mapping (NET_ETH)
#define PIN_ETH_MISO    16 // SPI0 RX
#define PIN_ETH_CS_N    17 // driven as a GPIO
#define PIN_ETH_SCK     18
#define PIN_ETH_MOSI    19 // SPI0 TX
#define PIN_ETH_RST_N   20
#define PIN_ETH_INT_N   21 // level-low while socket 0 has a frame waiting
#define ETH_SPI         spi0
#define ETH_SPI_HZ      (20 * 1000 * 1000)

// I2C addresses, verified against the backplane netlist (2026-08-30):
// TCA9548A A0=A1=A2=GND, TCA9539 A0=A1=GND. Blade parts sit behind the mux,
// one blade per channel, so identical per-blade addresses never conflict.
#define ADDR_TCA9548A   0x70
#define ADDR_TCA9539    0x74
#define ADDR_INA226     0x40  // per blade
#define ADDR_MPQ4242    0x61  // per blade

// TCA9548A channel N carries slot N+1 (SC0/SD0 = SCL1/SDA1); channels 6-7 spare.

// TCA9539 bit map (from backplane netlist, via 330R series networks RN5-RN8):
//   P00-P05 = EN1..EN6      output, active high (blades hold 100k pull-downs)
//   P06     = FAN           output, active high
//   P07     = tied to GND   keep as input
//   P10-P15 = PRES1#..PRES6# input, low = blade fully seated
//   P16,P17 = tied to GND   keep as input
#define TCA9539_EN_BIT(port)    (port)         // port 0-5 -> P00-P05
#define TCA9539_FAN_BIT         6              // P06
#define TCA9539_PRES_BIT(port)  (8 + (port))   // port 0-5 -> P10-P15
#define TCA9539_CONFIG_P0       0x80           // P07 input, P00-P06 outputs
#define TCA9539_CONFIG_P1       0xFF           // all of port 1 inputs
